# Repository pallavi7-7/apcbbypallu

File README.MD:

# A Slice of PCB
This is a PCB that represents a slice and wakes up along side you and grabs your attention the instant it gets light and you can customize how it does that either by shouting or dancing or just glowing
# Parts Used
Resistors x7, LED's x5, Battery Cell x2, Push Switch x3, Buzzer x1, Mini Motor x1, Photoresistor x1
# What Does it Do?
This is a simple PCB that when fully turned on, when light is present the LED's, mini motor and a buzzer and the buzzer and motir can be turned off and if you put it near a boo
# Some Glimpses

# Made by Pallavi Panthi
Slack Username: pallavipanthi0

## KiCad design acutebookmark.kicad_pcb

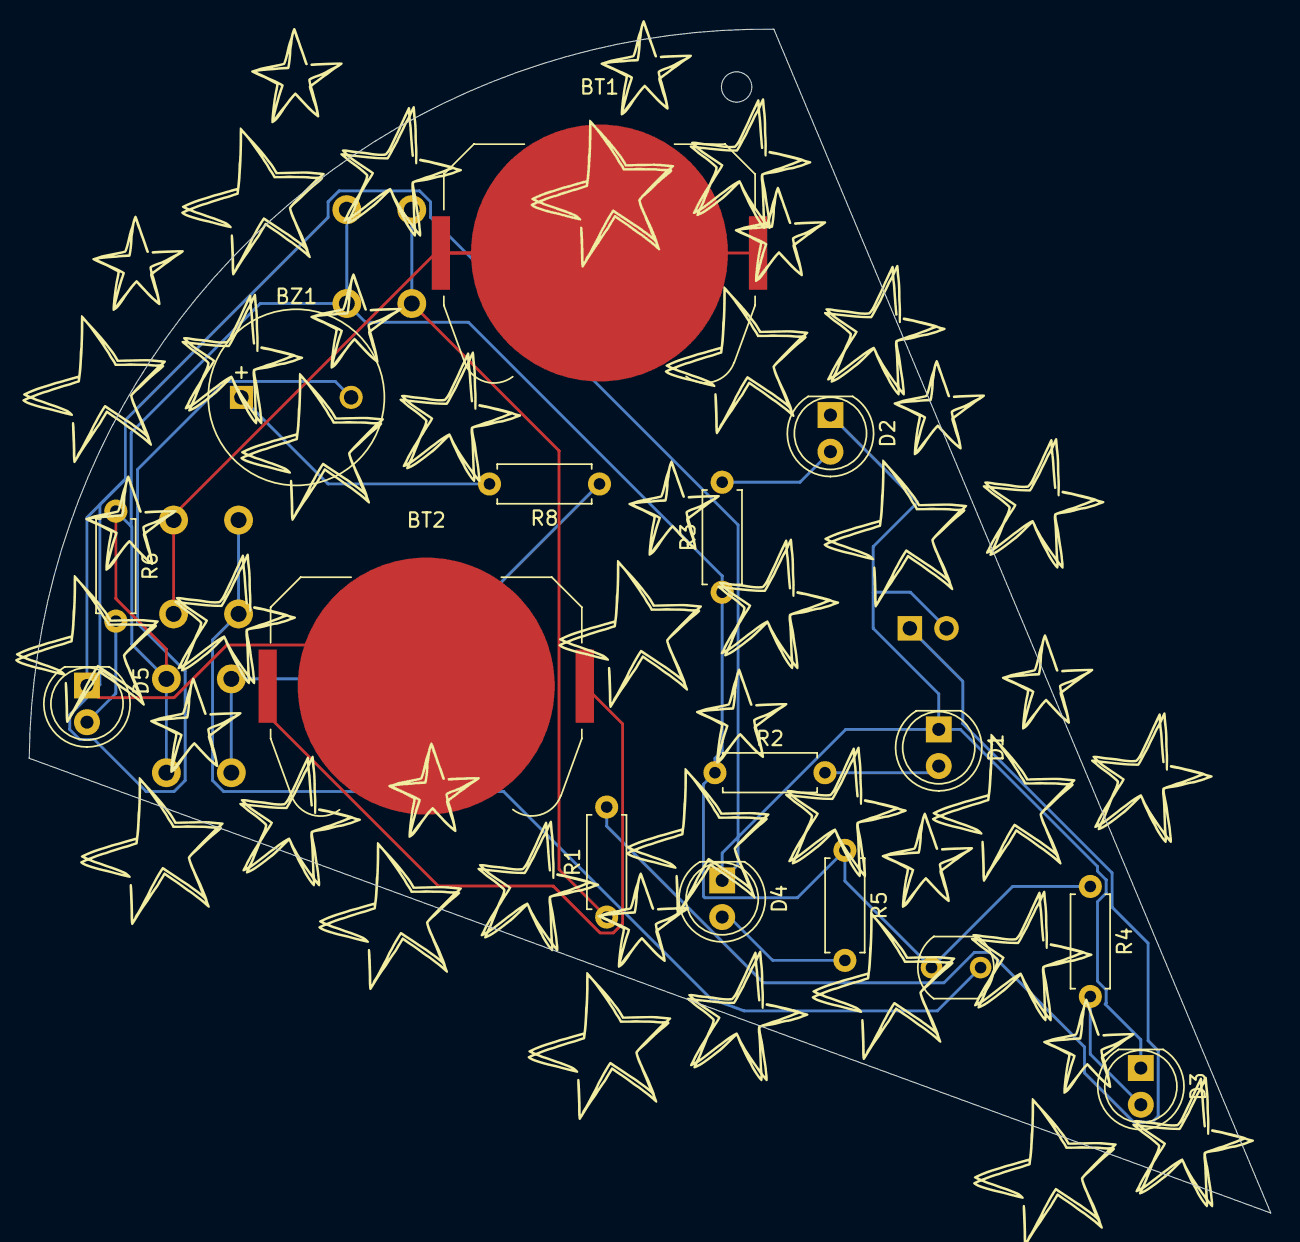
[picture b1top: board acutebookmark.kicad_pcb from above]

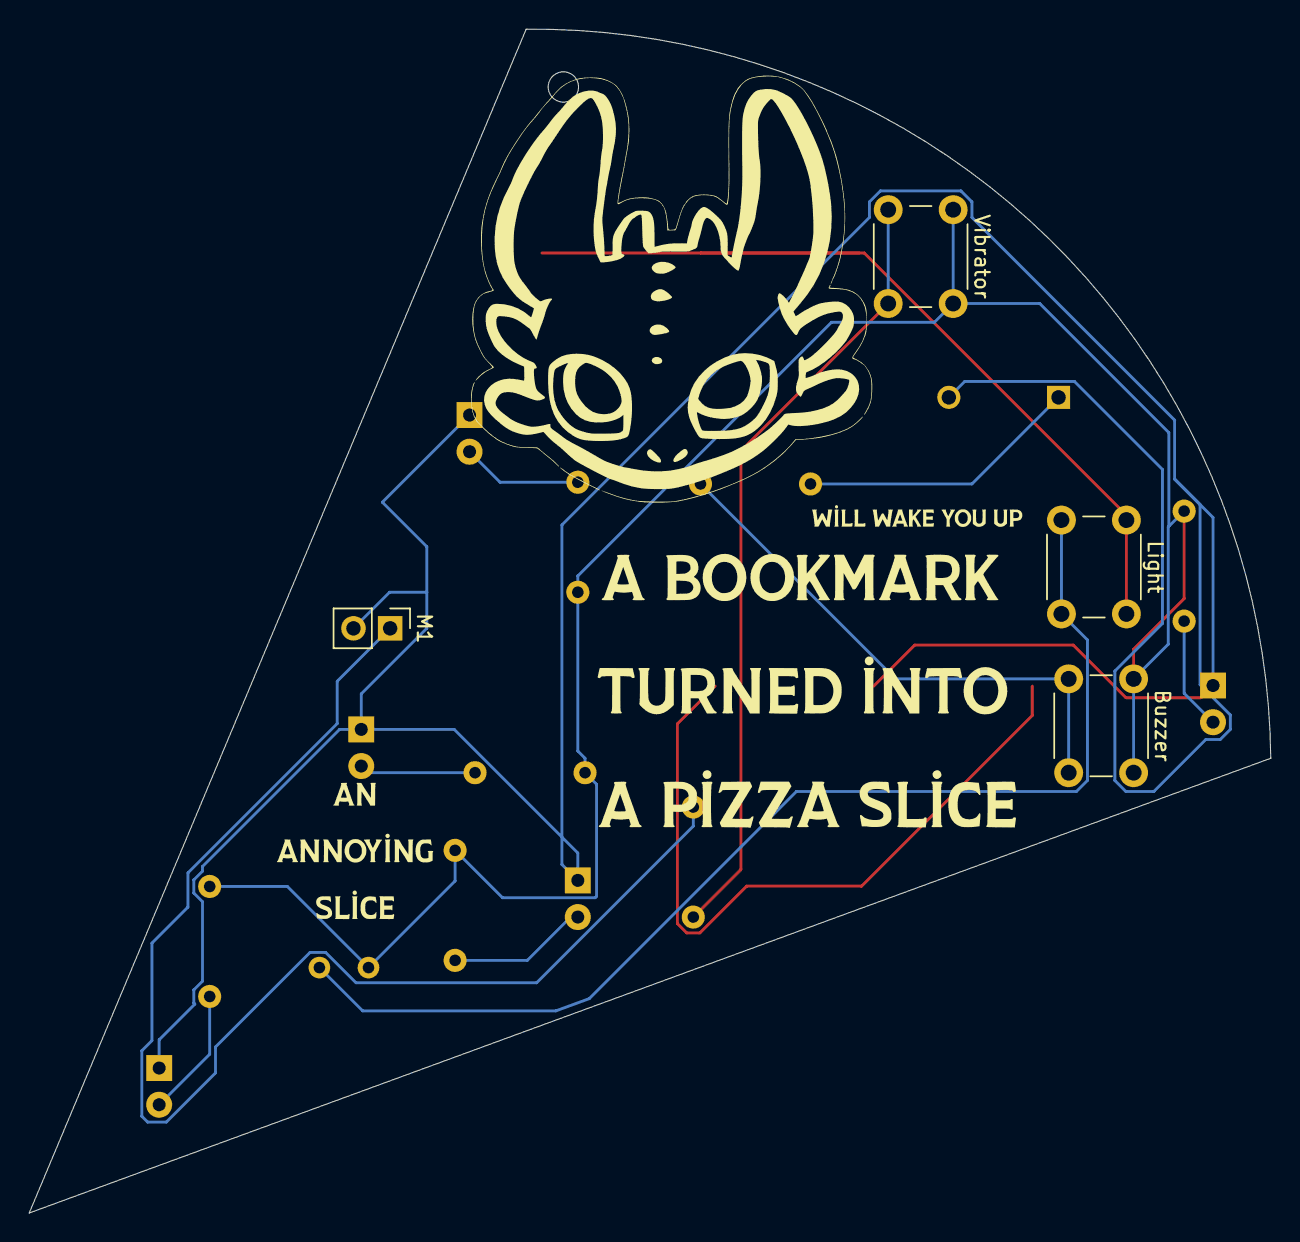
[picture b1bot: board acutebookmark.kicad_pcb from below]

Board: 2 copper layers, 86.0 x 82.0 mm, 20 parts (4 on the bottom side), 13 nets.

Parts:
BT1, BT2: Battery_Cell; BatteryHolder_Keystone_3034_1x20mm
BZ1: Buzzer; MagneticBuzzer_ProSignal_ABI-009-RC
Buzzer: SW_Push; SW_PUSH_6mm
D1, D2, D3, D4, D5: LED; LED_D5.0mm
Light: SW_Push; SW_PUSH_6mm
M1: Motor_DC; PinHeader_1x02_P2.54mm_Vertical
R1, R2, R3, R4, R5, R6, R8: R; R_Axial_DIN0207_L6.3mm_D2.5mm_P7.62mm_Horizontal
R7: LDR03; R_LDR_5.1x4.3mm_P3.4mm_Vertical
Vibrator: SW_Push; SW_PUSH_6mm

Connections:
unnamed: BT1.1 (+), Light.1
unnamed: BT2.2 (-), BZ1.2 (-), D1.1 (K), D2.1 (K), D3.1 (K), D4.1 (K), D5.1 (K), M1.2 (-)
unnamed: BZ1.1 (+), R8.2
unnamed: D1.2 (A), R2.2
unnamed: D2.2 (A), R3.2
unnamed: D3.2 (A), R4.2
unnamed: D4.2 (A), R5.2
unnamed: D5.2 (A), R6.2
unnamed: M1.1 (+), R1.2
unnamed: R1.1, Vibrator.2
unnamed: Buzzer.1, R2.1, R3.1, R4.1, R5.1, R6.1, R7.1, Vibrator.1
unnamed: Light.2, R7.2
unnamed: Buzzer.2, R8.1

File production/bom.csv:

Designator,Footprint,Quantity,Value,LCSC Part #
"BT1, BT2",BatteryHolder_Keystone_3034_1x20mm,2,Battery_Cell,
"BUZZER, LIGHT, VIBRATOR",SW_PUSH_6mm,3,SW_Push,
BZ1,MagneticBuzzer_ProSignal_ABI-009-RC,1,Buzzer,
"D1, D2, D3, D4, D5",LED_D5.0mm,5,LED,
M1,PinHeader_1x02_P2.54mm_Vertical,1,Motor_DC,
"R1, R2, R3, R4, R5, R6, R8",R_Axial_DIN0207_L6.3mm_D2.5mm_P7.62mm_Horizontal,7,R,
R7,R_LDR_5.1x4.3mm_P3.4mm_Vertical,1,LDR03,

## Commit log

2025-06-29 Uploaded some glimpses of the board
